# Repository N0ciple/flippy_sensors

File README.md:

# Flippy Sensors 🐬

flippy sensor is a WIP multi-sensor board for the flipper zero. It includes a SHT30 for temperature and humidity, a LSM6DS3TR-C for gyro and accelerometer and a PA1010D for GPS. A first batch is currently in production at JLCPCB.

## sensors list
- **PA1010D**: GPS/GNSS [datasheet](https://cdn-learn.adafruit.com/assets/assets/000/084/295/original/CD_PA1010D_Datasheet_v.03.pdf?1573833002)
- **LSM6DS3TR-C**: Accelerometer and gyroscope [datasheet](https://www.mouser.fr/datasheet/2/389/lsm6ds3tr_c-1761429.pdf)
- **SHT30**: Temperature and humidity [datasheet](https://www.mouser.com/datasheet/2/682/Sensirion_Humidity_Sensors_SHT3x_Datasheet_digital-971521.pdf)

All sensors communicate with I2C
| sensor      | I2C address |
| ----------- | ----------- |
| PA1010D     | `0x10`      |
| LSM6DS3TR-C | `0x6A`      |
| SHT30       | `0x44`      |

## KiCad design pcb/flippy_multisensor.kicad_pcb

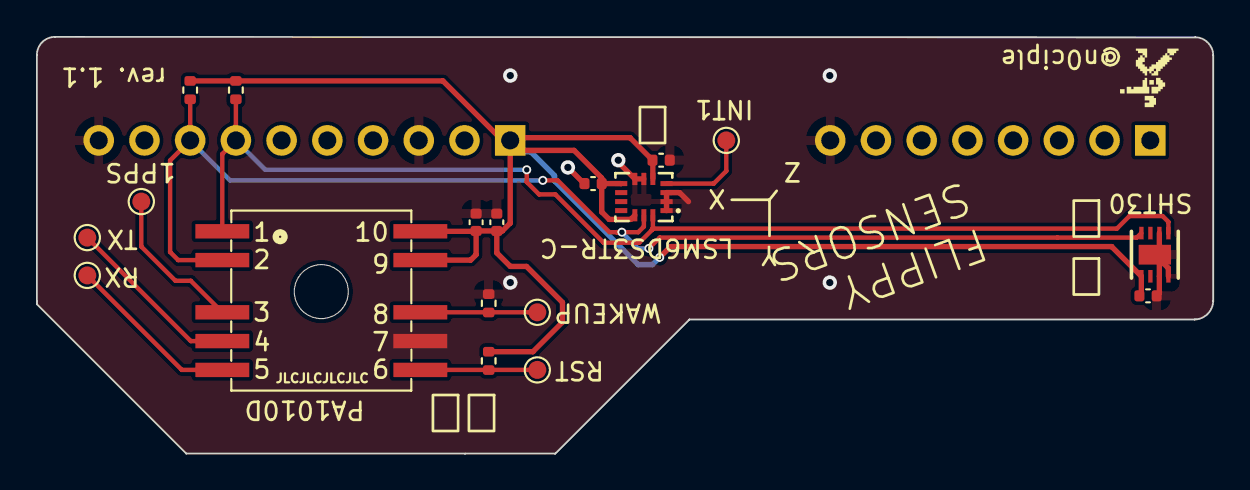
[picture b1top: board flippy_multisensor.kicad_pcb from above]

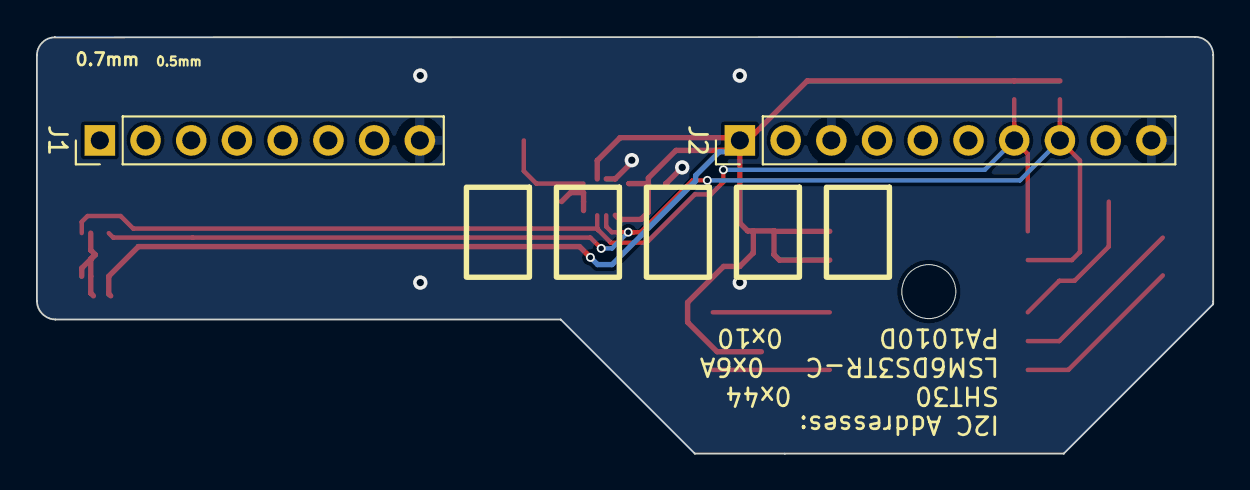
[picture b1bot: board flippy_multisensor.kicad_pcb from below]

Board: 2 copper layers, 65.4 x 23.2 mm, 20 parts (2 on the bottom side), 10 nets.

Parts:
1PPS: 1PPS; TestPoint_Pad_D1.0mm
C1, C2, C3, C5: 100n; C_0402_1005Metric
C4: 1u; C_0402_1005Metric
INT1: TestPoint; TestPoint_Pad_D1.0mm
J1: PINHD_1x8_Male; PinHeader_1x08_P2.54mm_Vertical
J2: PINHD_1x10_Male; PinHeader_1x10_P2.54mm_Vertical
R1, R2, R3, R4: 10k; R_0402_1005Metric
RST: reset pin; TestPoint_Pad_D1.0mm
RX: UART RX; TestPoint_Pad_D1.0mm
TX: UART TX; TestPoint_Pad_D1.0mm
U1: SHT30-DIS-B10KS; DFN-8_L2.5-W2.5-P0.50-BL-EP
U2: LSM6DS3TR-C; LGA-14_L3.0-W2.5-P0.50-TL
U3: PA1010D; PA1010D_footprint
WAKEUP: wakup pin; TestPoint_Pad_D1.0mm

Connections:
+3.3V: C1.1, C2.1, C3.1, C4.1, C5.1, J2.1, R1.2, R2.1, R4.1, U1.5 (VDD), U2.5 (VDDIO), U2.8 (VDD), U2.12 (CS), U3.9 (VBACKUP), U3.10 (VCC)
GND: C1.2, C2.2, C3.2, C4.2, C5.2, J1.8, J2.3, J2.10, R3.2, U1.2 (ADDR), U1.7 (R), U1.8 (VSS), U1.9 (EP), U2.1 (SDO/SA0), U2.2 (SDx), U2.3 (SCx), U2.6 (GND), U2.7 (GND), U3.7 (GND)
unnamed: INT1.1, U2.4 (INT1)
unnamed: 1PPS.1, U3.3 (1PPS)
unnamed: RX.1, U3.5 (RX)
unnamed: TX.1, U3.4 (TX)
unnamed: R3.1, U3.8 (WAKEUP), WAKEUP.1
unnamed: R4.2, RST.1, U3.6 (~RESET)
SCL: J2.8, R2.2, U1.4 (SCL), U2.13 (SCL), U3.2 (SCL)
SDA: J2.7, R1.1, U1.1 (SDA), U2.14 (SDA), U3.1 (SDA)

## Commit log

2024-02-19 add kicad files
2024-02-19 renaming
2024-02-19 Add PA1010D 3D model
2024-02-19 update libs
2024-02-19 Convert 3D model to STEP
2024-02-19 remove schematic backup
2024-02-19 update PCB
2024-02-19 add gitignore
2024-02-19 update PA1010D 3D model
2024-02-19 Change 3D background color for renders
2024-02-19 update test points labels
2024-02-19 add images
2024-02-26 correct the SHT30 i2c address on the label
2024-02-27 add app sources
2024-02-27 update github action
2024-07-21 Modifs for release
2024-07-21 ufbt format
2024-07-21 update github build workflow
2024-07-21 correct typo
2024-07-22 unique csv name at each launch
2024-07-22 update info screen management
2024-07-24 update github action to target multiple sdk
2024-11-25 add direnv
2024-11-25 add direnv v2
2024-11-25 add uv with flake
2024-11-25 add ufbt auto install
2024-11-26 update flake (remove ufbt installation)
2024-11-26 add alias for ufbt to uvx ufbt
